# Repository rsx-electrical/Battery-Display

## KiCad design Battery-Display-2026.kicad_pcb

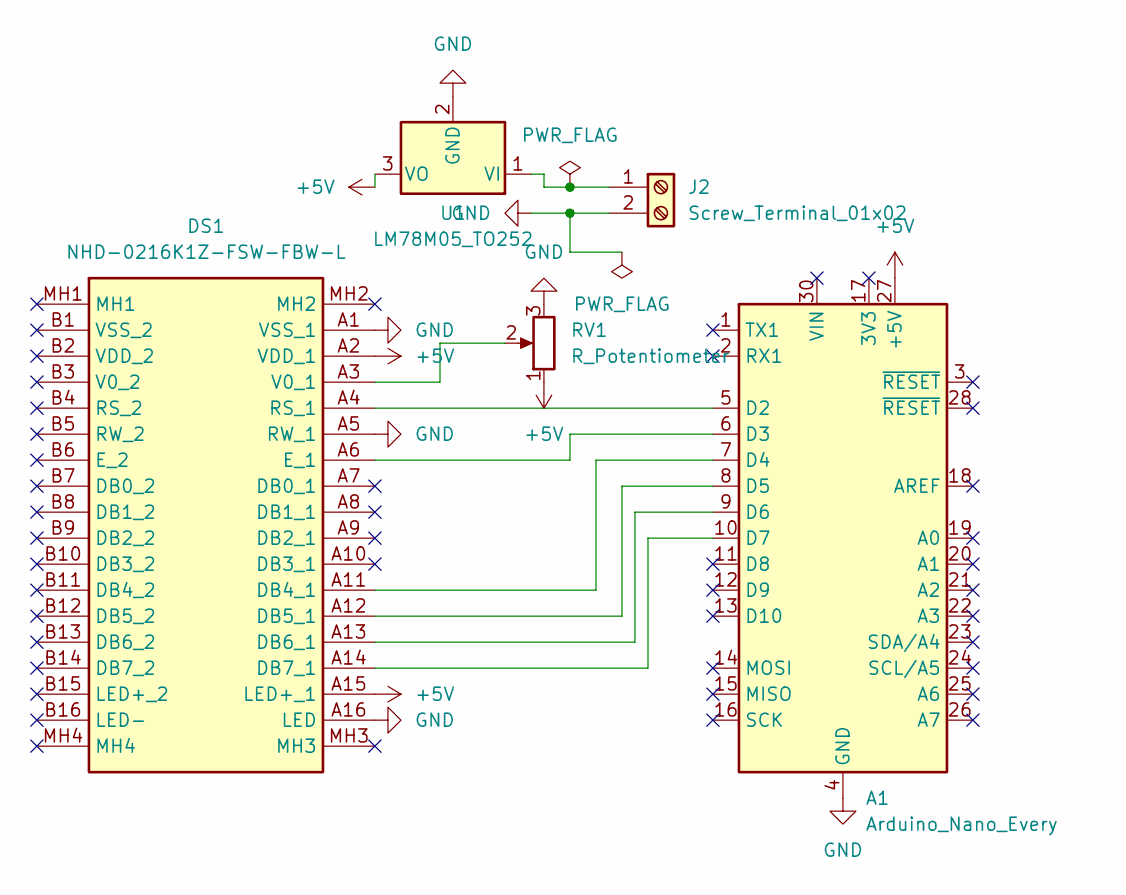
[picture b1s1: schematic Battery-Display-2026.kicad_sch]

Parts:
A1: Arduino_Nano_Every; Arduino_Nano
DS1: NHD-0216K1Z-FSW-FBW-L; NHD0216K1ZFSWFBWL; Mouser Part Number 763-0216K1Z-FSW-FBW
J2: Screw_Terminal_01x02; TerminalBlock_Phoenix_MKDS-1,5-2_1x02_P5.00mm_Horizontal
RV1: R_Potentiometer; R_Array_SIP4
U1: LM78M05_TO252; TO-252-2

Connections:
+5V: A1.27 (+5V), DS1.A2 (VDD_1), DS1.A15 (LED+_1), RV1.1, U1.3 (VO)
GND: A1.4 (GND), A1.29 (GND), DS1.A1 (VSS_1), DS1.A5 (RW_1), DS1.A16 (LED), J2.2, RV1.3, U1.2 (GND)
unnamed: A1.5 (D2), DS1.A4 (RS_1)
unnamed: A1.6 (D3), DS1.A6 (E_1)
unnamed: A1.7 (D4), DS1.A11 (DB4_1)
unnamed: A1.8 (D5), DS1.A12 (DB5_1)
unnamed: A1.9 (D6), DS1.A13 (DB6_1)
unnamed: A1.10 (D7), DS1.A14 (DB7_1)
unnamed: DS1.A3 (V0_1), RV1.2
unnamed: J2.1, U1.1 (VI)

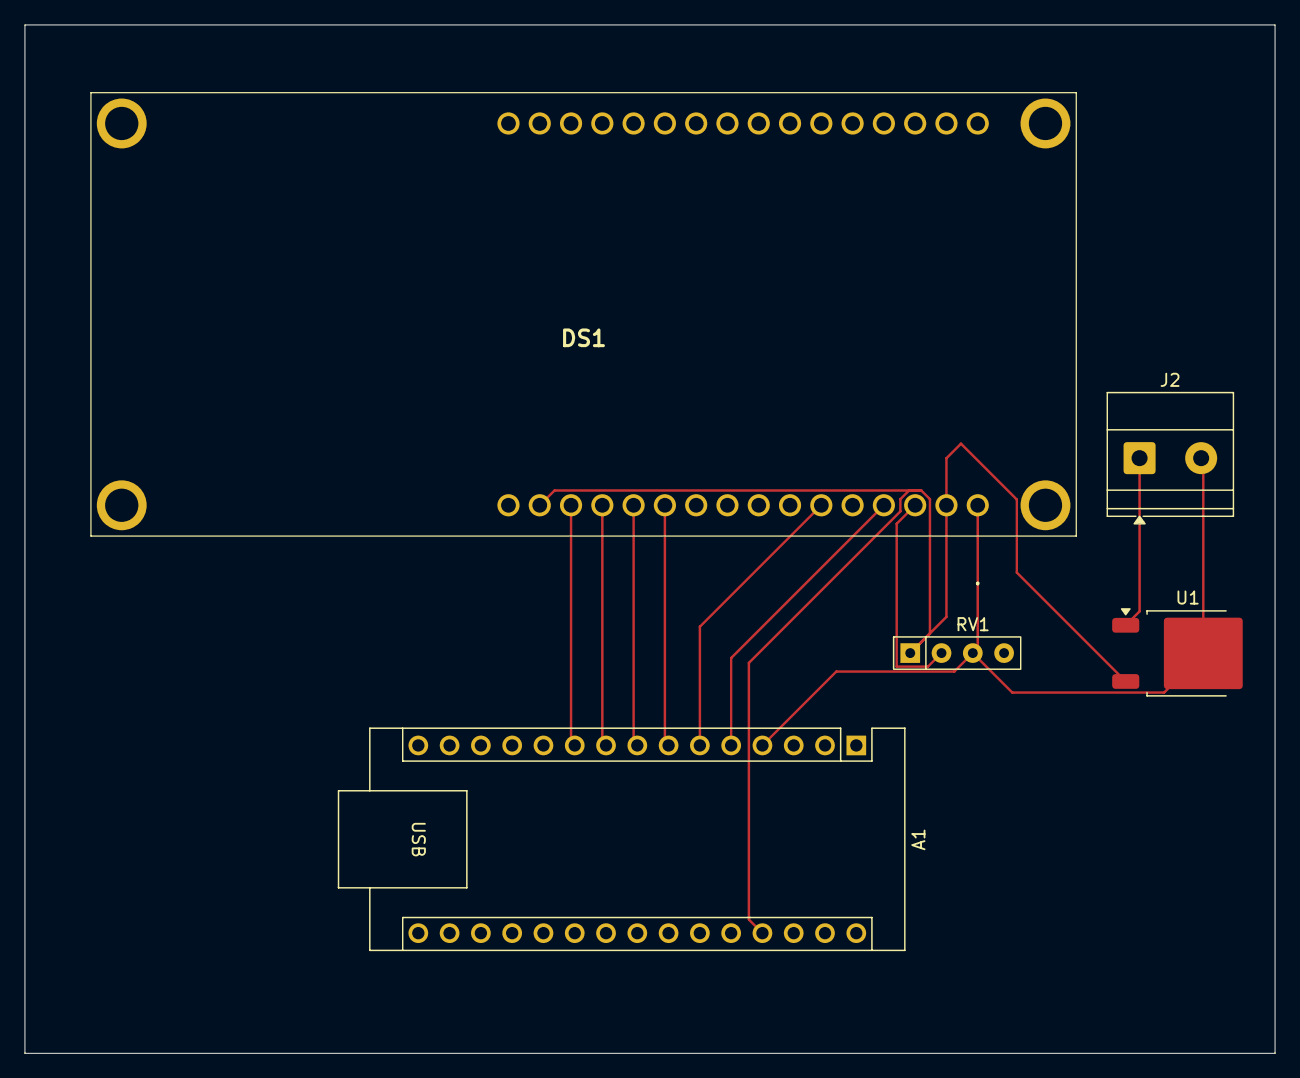
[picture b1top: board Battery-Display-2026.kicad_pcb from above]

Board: 2 copper layers, 101.5 x 83.5 mm, 5 parts (0 on the bottom side), 10 nets.

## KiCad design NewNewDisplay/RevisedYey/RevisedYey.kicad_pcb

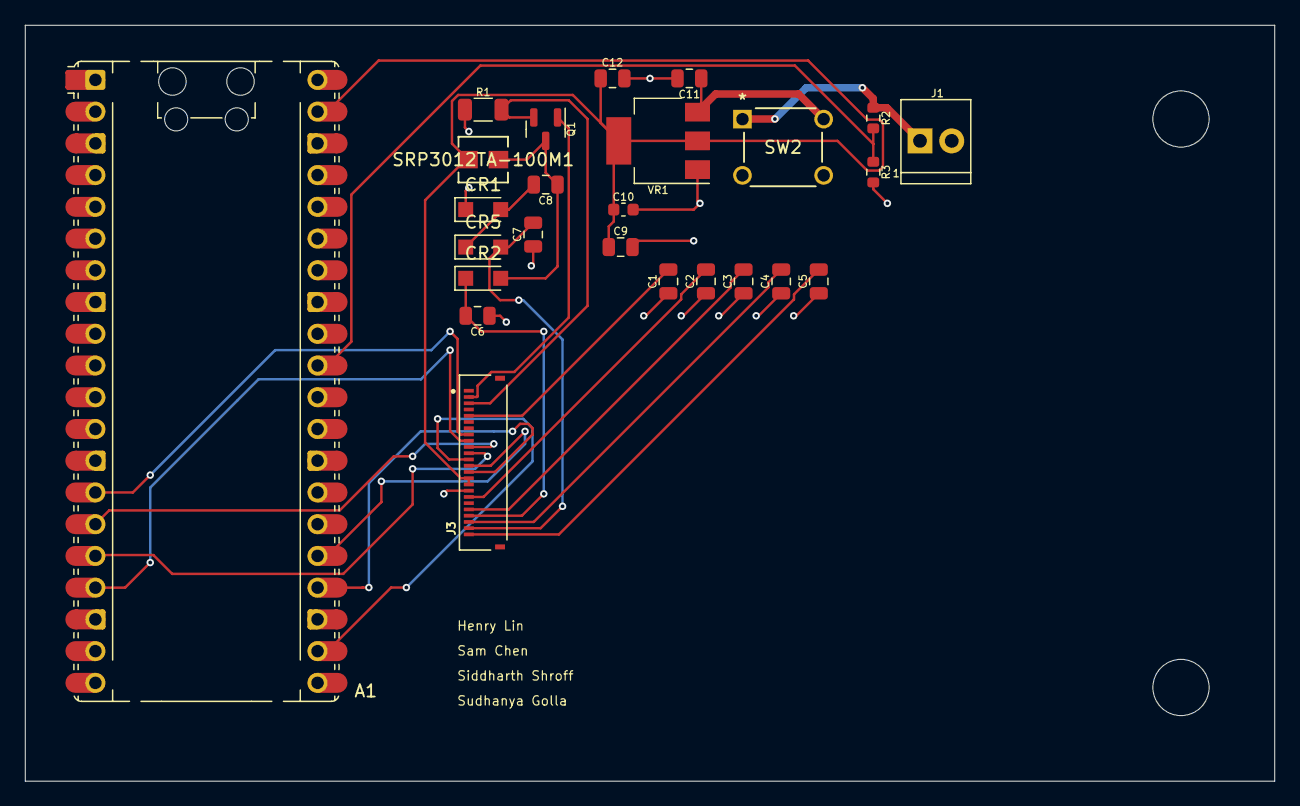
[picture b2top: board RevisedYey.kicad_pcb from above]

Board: 2 copper layers, 100.0 x 60.5 mm, 27 parts (0 on the bottom side), 23 nets.

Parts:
A1: RaspberryPi_Pico; RaspberryPi_Pico_Common_Unspecified
C1, C2, C3, C4, C5, C6, C7: 1u; C_0805_2012Metric
C8, C9: 4u7; C_0805_2012Metric
C10: 0u1; C_0603_1608Metric
C11, C12: 10u; C_0805_2012Metric
CR1, CR2, CR5: SS2040FL_R1_00001; Nexperia_CFP3_SOD-123W
H1, H2: M4 PLAIN; MountingHole_4.5mm
J1: Screw_Terminal_2x2.54; Wurth_691210910002
J3: FH34SRJ-24S-0.5SH_99_; HRS_FH34SRJ-24S-0.5SH_99_
Q1: ZXM61N03F; SOT-23
R1: 0.47R; R_1206_3216Metric
R2: 1M; R_0603_1608Metric
R3: 249K_0.1%; R_0603_1608Metric
SRP3012TA-100M1: 10uH; IND_SRP3012TA_BRN
SW2: Button-THT - 2-1825910-7; 2-1825910-7
VR1: NCP1117-3.3V; SOT-223-3_TabPin2

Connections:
+16V: J1.1, R2.1, SW2.1
GND: A1.3 (GND), A1.8 (GND), A1.13 (GND), A1.18 (GND), A1.23 (GND), A1.28 (GND), A1.38 (GND), C1.1, C2.1, C3.1, C4.1, C5.1, C6.1, C7.1, C9.2, C10.2, C11.2, C12.2, CR1.1, J1.2, J3.17, R1.1, R3.2, VR1.1 (GND)
GP10 - Pin 8 BS: A1.14 (GPIO10), J3.8
GP11 - Pin 10 RST: A1.15 (GPIO11), J3.10
GP12 - Pin 11 DC: A1.16 (GPIO12), J3.11
GP13 - Pin 9 Busy: A1.17 (GPIO13), J3.9
GP17 - Pin 12 CSB: A1.22 (GPIO17), J3.12
GP18 - Pin 14 SDA: A1.24 (GPIO18), J3.14
GP19 - Pin 13 SCL: A1.25 (GPIO19), J3.13
unnamed: C1.2, J3.5
unnamed: C2.2, J3.18
unnamed: C3.2, J3.20
unnamed: C4.2, J3.22
unnamed: C5.2, J3.24
unnamed: C6.2, CR2.1, J3.21
unnamed: C7.2, CR5.2, J3.23
unnamed: C8.2, CR1.2, CR5.1
unnamed: C8.1, CR2.2, Q1.3 (D), SRP3012TA-100M1.2
unnamed: J3.2, Q1.1 (G)
unnamed: J3.3, Q1.2 (S), R1.2
unnamed: C11.1, SW2.2, VR1.3 (VI)
PWR Board/Pico: A1.39 (VSYS), C9.1, C10.1, C12.1, J3.15, J3.16, SRP3012TA-100M1.1, VR1.2 (VO)
Vdiv pico: A1.31 (GPIO26_ADC0), R2.2, R3.1

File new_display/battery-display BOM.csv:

"Reference","Qty","Value","DNP","Exclude from BOM","Exclude from Board","Footprint","Datasheet"
"A1","1","RaspberryPi_Pico","","","","Module:RaspberryPi_Pico_Common_Unspecified","https://datasheets.raspberrypi.com/pico/pico-datasheet.pdf"
"C1,C2,C3,C4,C5,C6,C7","7","1u","","","","rsx_capacitors:C_0805_2012Metric","~"
"C8,C9","2","4u7","","","","rsx_capacitors:C_0805_2012Metric","~"
"C10","1","0u1","","","","rsx_capacitors:C_0603_1608Metric","~"
"C11,C12,C13","3","10u","","","","rsx_capacitors:C_0805_2012Metric","~"
"CR1,CR2,CR5","3","SS2040FL_R1_00001","","","","Diode_SMD:Nexperia_CFP3_SOD-123W","https://www.panjit.com.tw/upload/datasheet/SS2020FL_SERIES.pdf"
"H1,H2,H3,H4","4","M4 PLAIN","","Excluded from BOM","","rsx_misc:MountingHole_4.5mm","~"
"J1","1","Screw_Terminal_2x2.54","","","","rsx_headers_screw:Wurth_691210910002","~"
"J3","1","FH34SRJ-24S-0.5SH_99_","","","","rsx_headers_communications:HRS_FH34SRJ-24S-0.5SH_99_",""
"Q1,Q3","2","ZXM61N03F","","","","rsx_packages_TO_SOT:SOT-23","https://www.diodes.com/assets/Datasheets/ZXM61N03F.pdf"
"R1","1","0.47R","","","","rsx_resistors:R_1206_3216Metric","https://www.yageogroup.com/content/Resource%20Library/Datash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"
"R2","1","1M","","","","rsx_resistors:R_0603_1608Metric","~"
"R3","1","249K_0.1%","","","","rsx_resistors:R_0603_1608Metric","~"
"R4","1","330R","","","","rsx_resistors:R_0603_1608Metric","~"
"R5","1","100K","","","","rsx_resistors:R_0603_1608Metric","~"
"SRP3012TA-100M1","1","10uH","","","","rsx_inductors:IND_SRP3012TA_BRN","https://www.bourns.com/docs/Product-Datasheets/SRP3012TA.pdf"
"SW2","1","Button-THT - 2-1825910-7","","","","rsx_HID:2-1825910-7","https://www.te.com/usa-en/product-2-1825910-7.datasheet.pdf"
"VR1","1","NCP1117-3.3V","","","","rsx_packages_TO_SOT:SOT-223-3_TabPin2",""

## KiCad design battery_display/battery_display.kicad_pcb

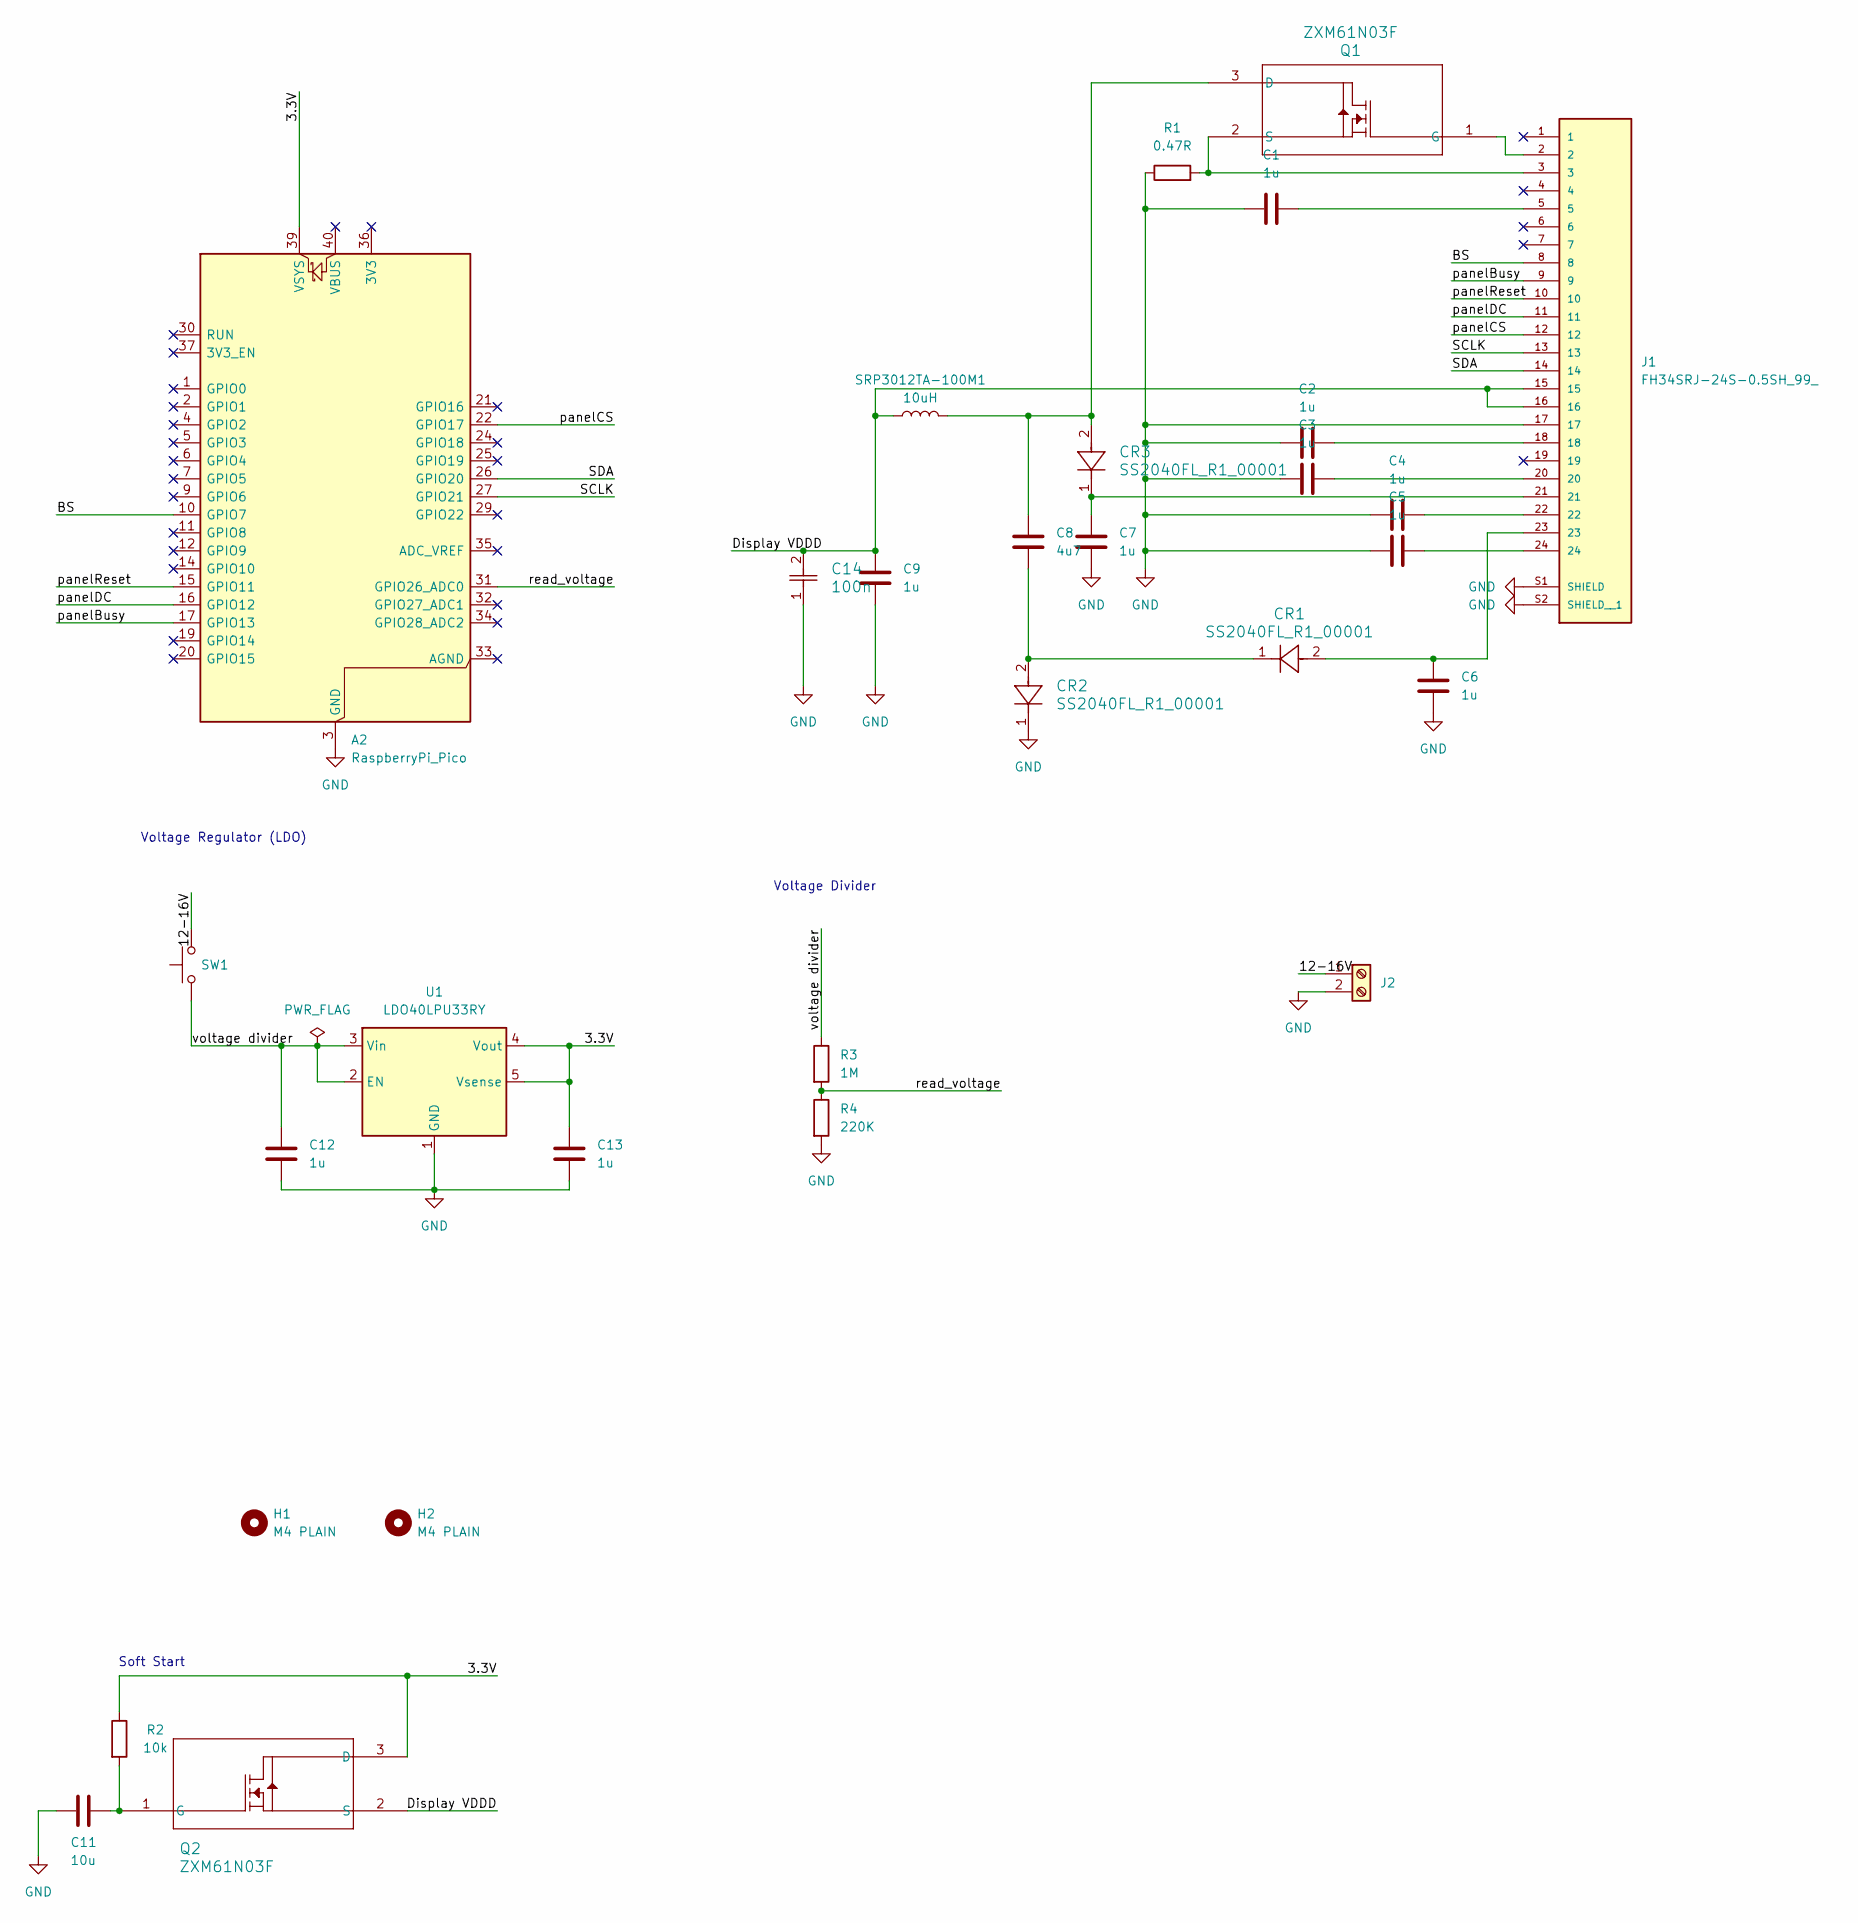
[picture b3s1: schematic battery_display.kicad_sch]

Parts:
A2: RaspberryPi_Pico; RaspberryPi_Pico_Common_Unspecified
C1, C2, C3, C4, C5, C6, C7, C9: 1u; C_0603_1608Metric; MPN CL10A105KA8NNNC
C8: 4u7; C_0805_2012Metric; MPN CL21A475KAQNNNE
C11: 10u; C_0805_2012Metric; MPN GRM21BR61H106KE43L
C12, C13: 1u; C_0805_2012Metric; MPN CL21B105KBFNNNE
C14: 100n; CAPC17595_95N_KEM; MPN C0603C104K5RACTU
CR1, CR2, CR3: SS2040FL_R1_00001; Nexperia_CFP3_SOD-123W; MPN SS2040FL_R1_00001
H1, H2: M4 PLAIN; MountingHole_4.5mm
J1: FH34SRJ-24S-0.5SH_99_; HRS_FH34SRJ-24S-0.5SH_99_; PARTREV NA
J2: Screw_Terminal_2x2.54; Wurth_691210910002; MPN 691210910002
Q1, Q2: ZXM61N03F; SOT-23; MPN ZXM61N03FTA
R1: 0.47R; R_1206_3216Metric; MPN RL1206FR-070R47L
R2: 10k; R_0603_1608Metric; MPN RMCF0603JT10K0
R3: 1M; R_0603_1608Metric; MPN ERJ-3EKF1004V
R4: 220K; R_0603_1608Metric; MPN RMCF0603FT220K
SRP3012TA-100M1: 10uH; IND_SRP3012TA_BRN; MPN SRP3012TA-100M
SW1: Button-THT - 2-1825910-7; 2-1825910-7; MPN 2-1825910-7
U1: LDO40LPU33RY; DFN-6-1EP_3x3mm_P0.95mm_EP1.7x2.6mm

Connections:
/3.3V: A2.39 (VSYS), C13.1, Q2.3 (D), R2.1, U1.4 (Vout), U1.5 (Vsense)
/12-16V: J2.1, SW1.2
/BS: A2.10 (GPIO7), J1.8
/Display VDDD: C9.1, C14.2, J1.15, J1.16, Q2.2 (S), SRP3012TA-100M1.1
/SCLK: A2.27 (GPIO21), J1.13
/SDA: A2.26 (GPIO20), J1.14
/panelBusy: A2.17 (GPIO13), J1.9
/panelCS: A2.22 (GPIO17), J1.12
/panelDC: A2.16 (GPIO12), J1.11
/panelReset: A2.15 (GPIO11), J1.10
/read_voltage: A2.31 (GPIO26_ADC0), R3.2, R4.1
/voltage divider: C12.1, R3.1, SW1.1, U1.2 (EN), U1.3 (Vin)
GND: A2.3 (GND), A2.8 (GND), A2.13 (GND), A2.18 (GND), A2.23 (GND), A2.28 (GND), A2.38 (GND), C1.1, C2.1, C3.1, C4.1, C5.1, C6.2, C7.2, C9.2, C11.2, C12.2, C13.2, C14.1, CR2.1, J1.17, J1.S1 (SHIELD), J1.S2 (SHIELD__1), J2.2, R1.1, R4.2, U1.1 (GND), U1.7 (GND)
unnamed: C1.2, J1.5
unnamed: C2.2, J1.18
unnamed: C3.2, J1.20
unnamed: C4.2, J1.22
unnamed: C5.2, J1.24
unnamed: C6.1, CR1.2, J1.23
unnamed: C7.1, CR3.1, J1.21
unnamed: C8.2, CR1.1, CR2.2
unnamed: C8.1, CR3.2, Q1.3 (D), SRP3012TA-100M1.2
unnamed: J1.2, Q1.1 (G)
unnamed: J1.3, Q1.2 (S), R1.2
unnamed: C11.1, Q2.1 (G), R2.2

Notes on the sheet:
Voltage Divider
Soft Start
Voltage Regulator (LDO)

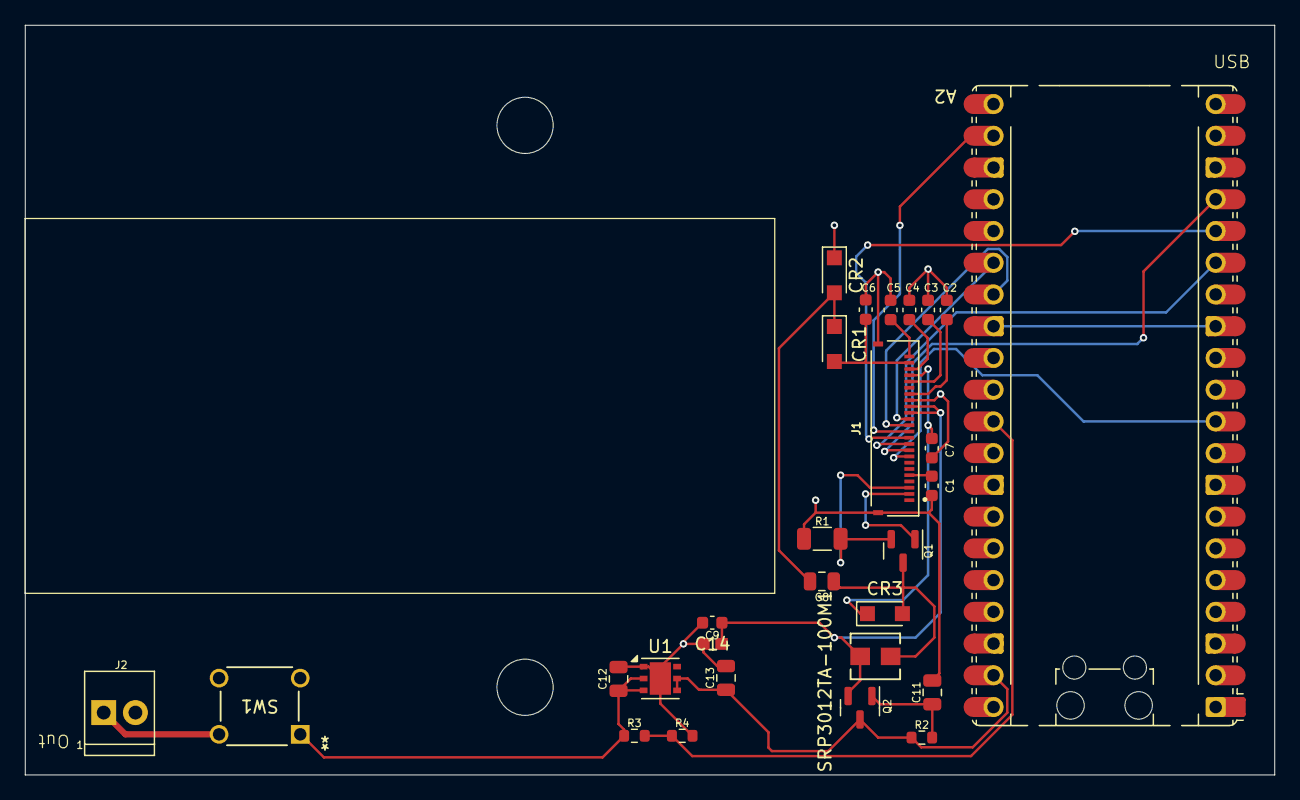
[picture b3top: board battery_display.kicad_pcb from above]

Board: 2 copper layers, 100.0 x 60.0 mm, 30 parts (0 on the bottom side), 25 nets.

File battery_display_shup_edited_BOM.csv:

"Id";"Designator";"Footprint";"Quantity";"Designation";"Supplier and ref";
1;"R1,R2";"R_1206_3216Metric";2;"0.47R";;;
2;"CR3,CR4,CR1";"Nexperia_CFP3_SOD-123W";3;"SS2040FL_R1_00001";;;
3;"Q2,Q1";"SOT-23";2;"ZXM61N03F";;;
4;"C9,C3,C6,C5,C4,C7,C1,C8,C2";"C_0805_2012Metric";9;"1u";;;
5;"VR1";"SOT-223-3_TabPin2";1;"NCP1117-3.3V";;;
6;"C10,C12";"C_0805_2012Metric";2;"10u";;;
7;"C11";"C_0603_1608Metric";1;"0u1";;;
8;"R3";"R_0603_1608Metric";1;"1M";;;
9;"SRP3012TA-100M1";"IND_SRP3012TA_BRN";1;"10uH";;;
10;"J2";"Wurth_691210910002";1;"Screw_Terminal_2x2.54";;;
11;"J1";"HRS_FH34SRJ-24S-0.5SH_99_";1;"FH34SRJ-24S-0.5SH_99_";;;
12;"R4";"R_0603_1608Metric";1;"220K";;;
13;"A1";"RaspberryPi_Pico_Common_Unspecified";1;"RaspberryPi_Pico";;;
14;"SW1";"2-1825910-7";1;"Button-THT - 2-1825910-7";;;

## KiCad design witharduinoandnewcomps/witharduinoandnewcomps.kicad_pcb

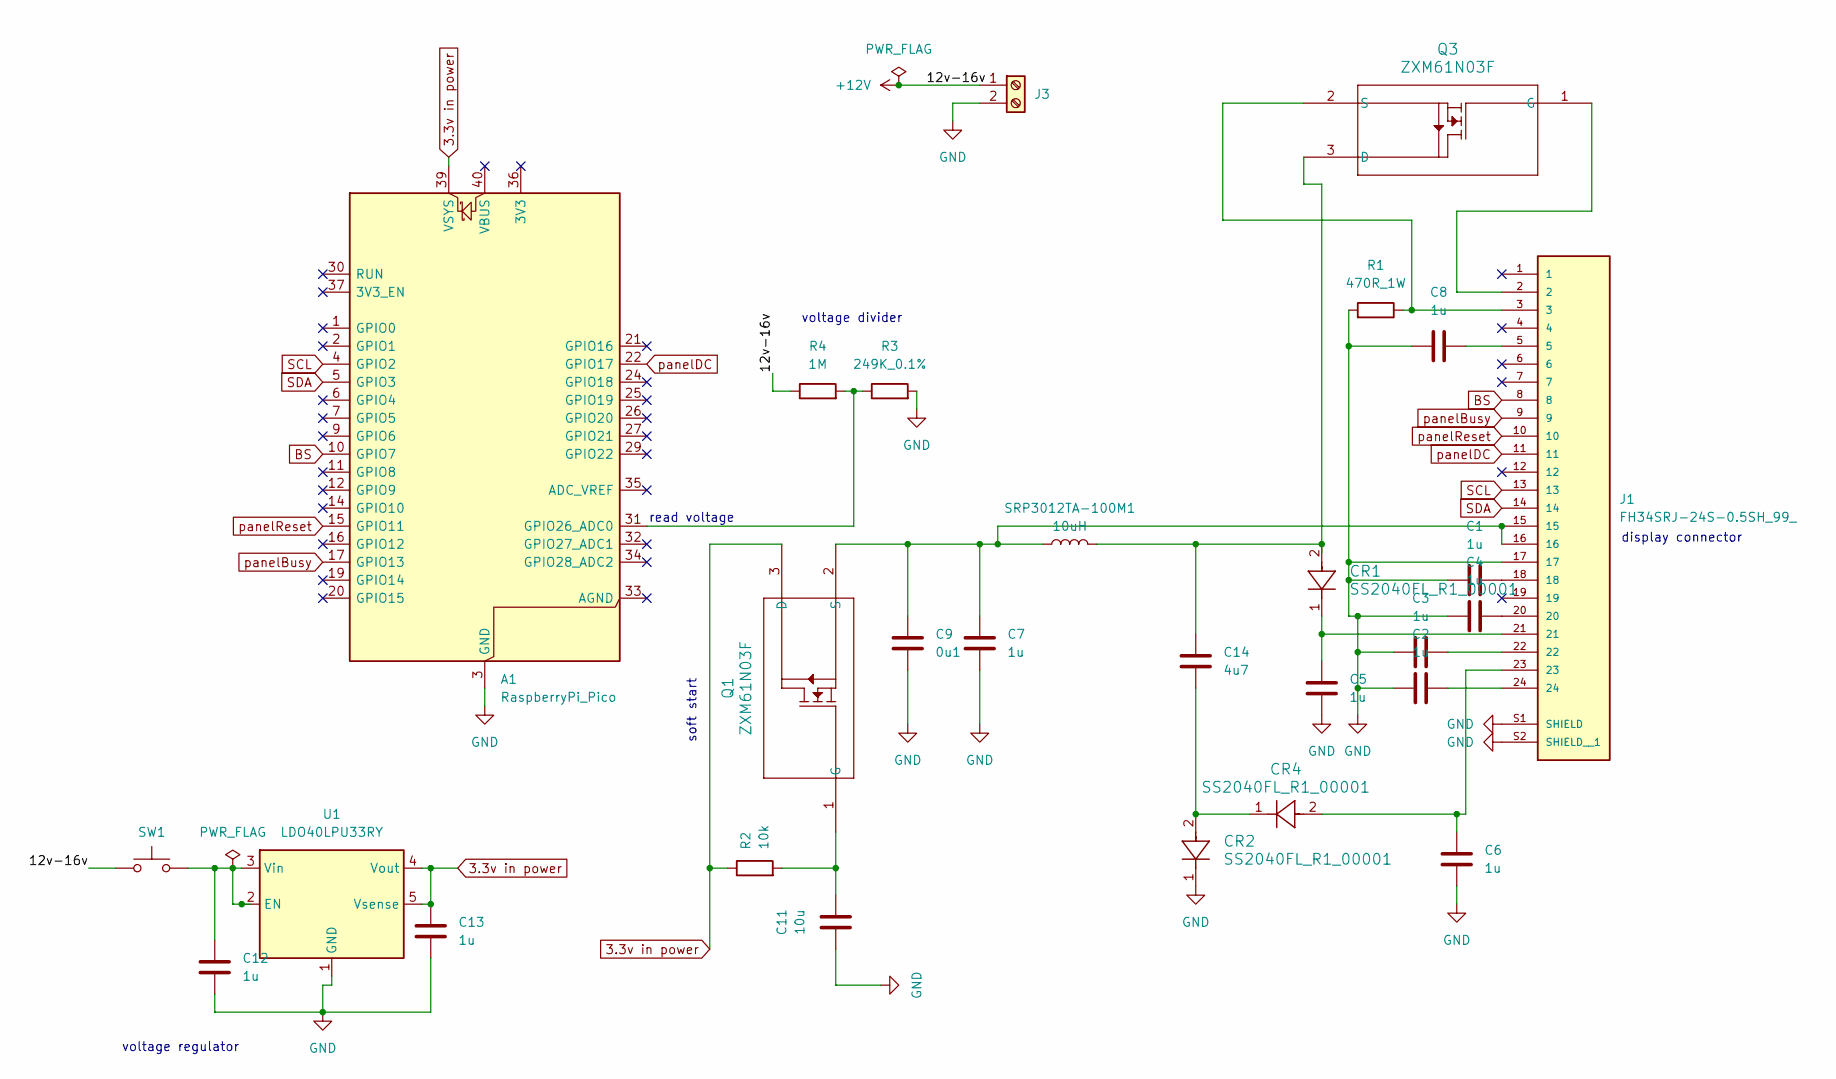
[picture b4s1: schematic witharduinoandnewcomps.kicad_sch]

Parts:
A1: RaspberryPi_Pico; RaspberryPi_Pico_Common_Unspecified
C1, C2, C3, C4, C5, C6, C7, C8, C12, C13: 1u; C_0805_2012Metric; MPN CL21B105KBFNNNE
C9: 0u1; C_0603_1608Metric; MPN C1608X7R1H104K080AA
C11: 10u; C_0805_2012Metric; MPN GRM21BR61H106KE43L
C14: 4u7; C_0805_2012Metric; MPN CL21A475KAQNNNE
CR1, CR2, CR4: SS2040FL_R1_00001; Nexperia_CFP3_SOD-123W; MPN SS2040FL_R1_00001
J1: FH34SRJ-24S-0.5SH_99_; HRS_FH34SRJ-24S-0.5SH_99_; PARTREV NA
J3: Screw_Terminal_2x2.54; Wurth_691210910002; MPN 691210910002
Q1, Q3: ZXM61N03F; SOT-23; MPN ZXM61N03FTA
R1: 470R_1W; R_2512_6332Metric; MPN RC2512FK-07470RL
R2: 10k; R_0603_1608Metric; MPN RMCF0603JT10K0
R3: 249K_0.1%; R_0603_1608Metric; MPN RC0603FR-07249KL
R4: 1M; R_0603_1608Metric; MPN ERJ-3EKF1004V
SRP3012TA-100M1: 10uH; IND_SRP3012TA_BRN; MPN SRP3012TA-100M
SW1: Button-THT - 2-1825910-7; 2-1825910-7; MPN 2-1825910-7
U1: LDO40LPU33RY; DFN-6-1EP_3x3mm_P0.95mm_EP1.7x2.6mm

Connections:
3.3v in power: A1.39 (VSYS), C13.1, Q1.3 (D), R2.1, U1.4 (Vout), U1.5 (Vsense)
+12V: J3.1, R4.1, SW1.1
BS: A1.10 (GPIO7), J1.8
GND: A1.3 (GND), A1.8 (GND), A1.13 (GND), A1.18 (GND), A1.23 (GND), A1.28 (GND), A1.38 (GND), C1.1, C2.1, C3.1, C4.1, C5.1, C6.1, C7.1, C8.1, C9.2, C11.1, C12.2, C13.2, CR2.1, J1.17, J1.S1 (SHIELD), J1.S2 (SHIELD__1), J3.2, R1.1, R3.2, U1.1 (GND), U1.7 (GND)
unnamed: A1.31 (GPIO26_ADC0), R3.1, R4.2
unnamed: C1.2, J1.18
unnamed: C2.2, J1.24
unnamed: C3.2, J1.22
unnamed: C4.2, J1.20
unnamed: C5.2, CR1.1, J1.21
unnamed: C6.2, CR4.2, J1.23
unnamed: C8.2, J1.5
unnamed: C14.2, CR2.2, CR4.1
unnamed: C11.2, Q1.1 (G), R2.2
unnamed: C7.2, C9.1, J1.15, J1.16, Q1.2 (S), SRP3012TA-100M1.1
unnamed: C14.1, CR1.2, Q3.3 (D), SRP3012TA-100M1.2
unnamed: J1.2, Q3.1 (G)
unnamed: J1.3, Q3.2 (S), R1.2
unnamed: C12.1, SW1.2, U1.2 (EN), U1.3 (Vin)
SCL: A1.4 (GPIO2), J1.13
SDA: A1.5 (GPIO3), J1.14
panelBusy: A1.17 (GPIO13), J1.9
panelDC: A1.22 (GPIO17), J1.11
panelReset: A1.15 (GPIO11), J1.10

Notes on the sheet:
soft start
voltage divider
display connector
read voltage
voltage regulator

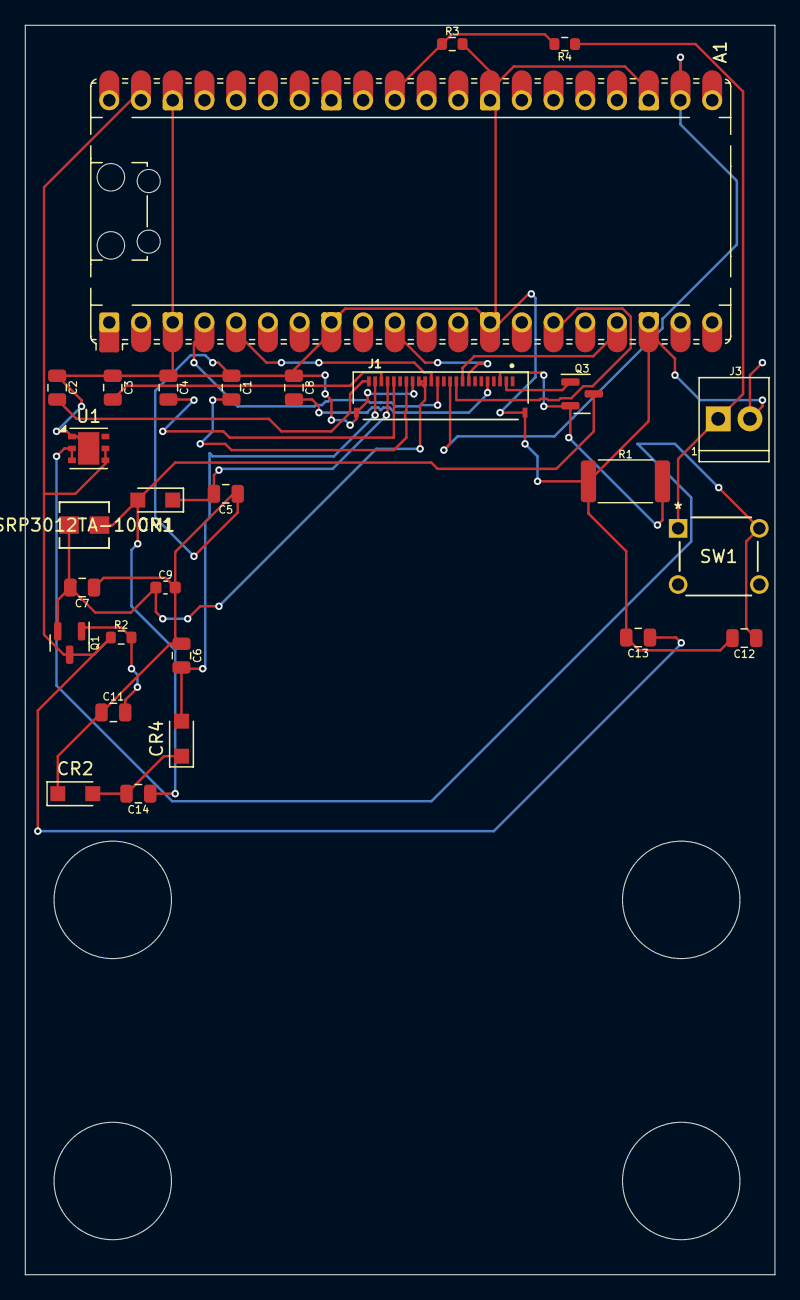
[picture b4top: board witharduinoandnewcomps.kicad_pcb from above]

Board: 2 copper layers, 60.0 x 100.0 mm, 28 parts (0 on the bottom side), 24 nets.

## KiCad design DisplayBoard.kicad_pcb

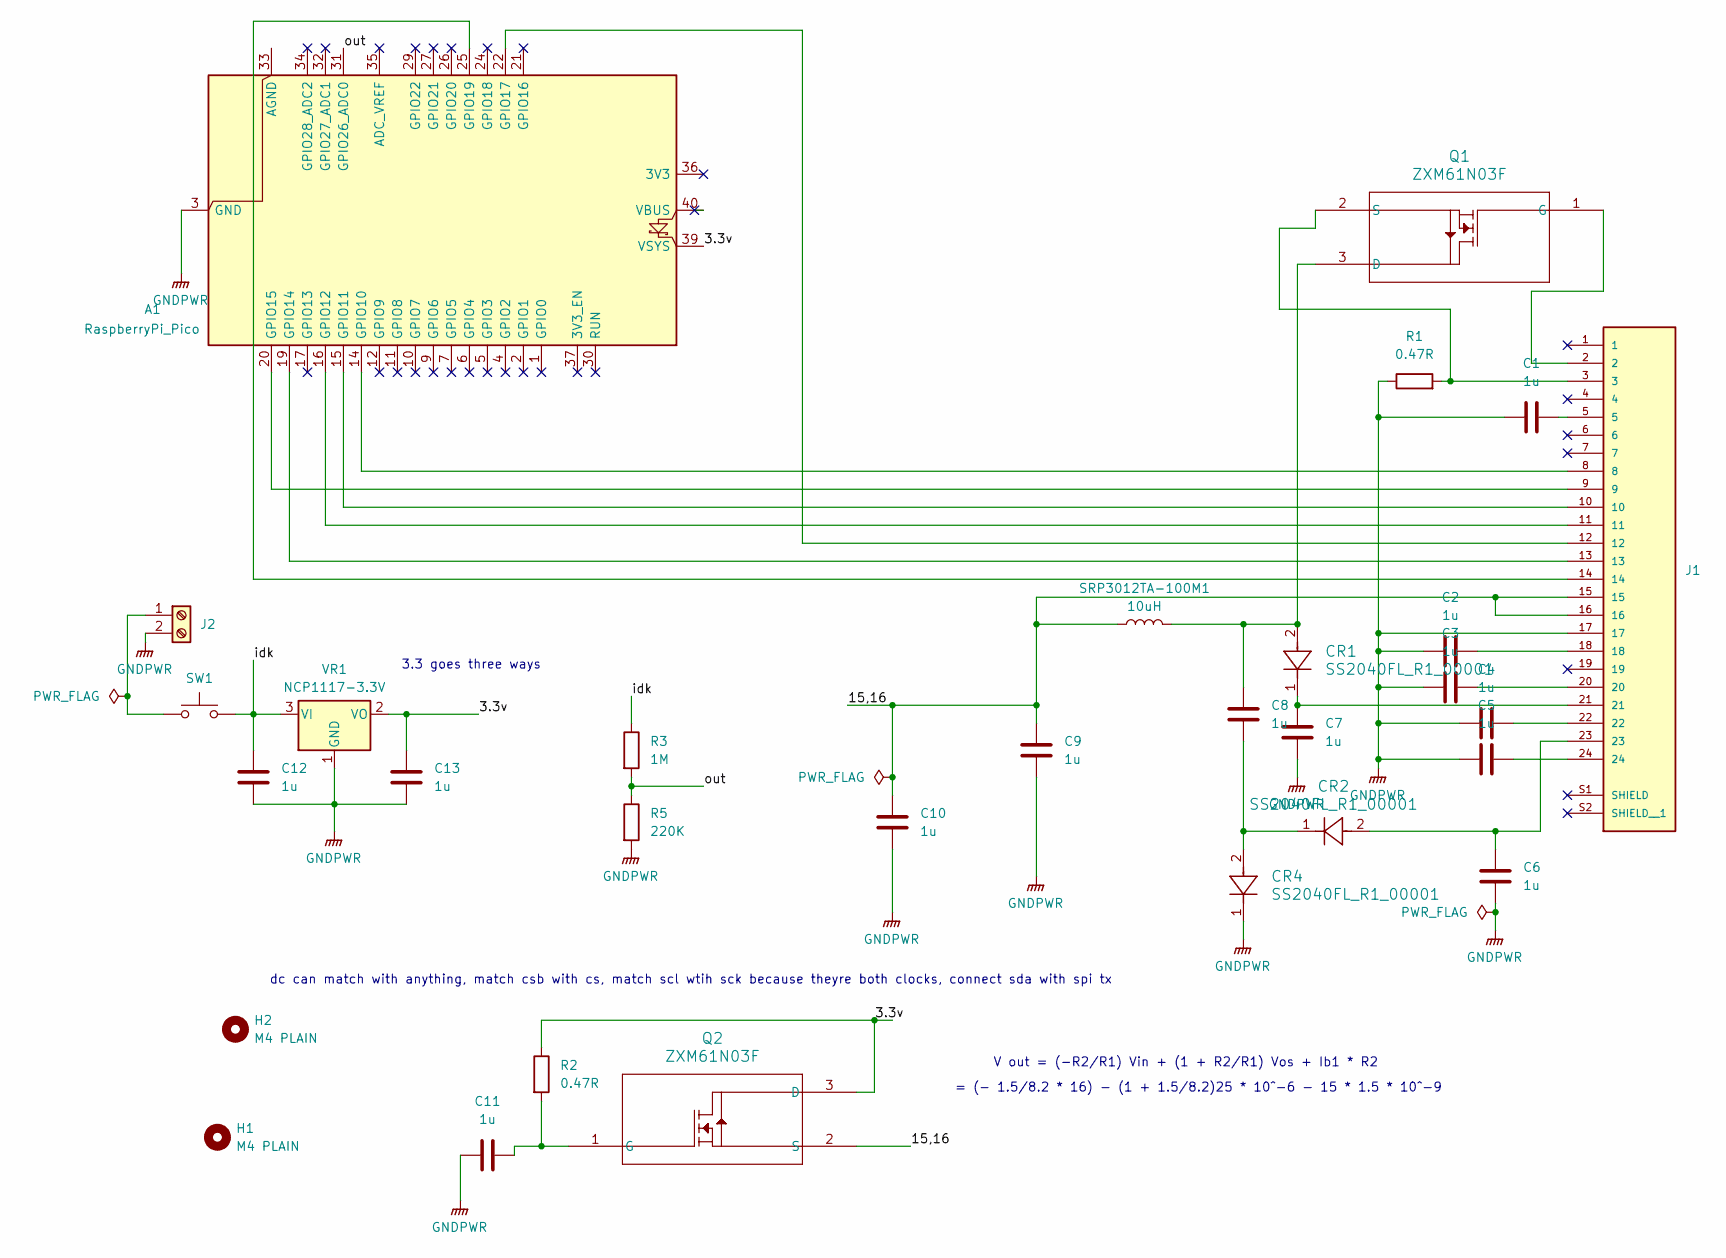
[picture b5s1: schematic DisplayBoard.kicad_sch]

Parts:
A1: RaspberryPi_Pico; RaspberryPi_Pico_Common_Unspecified
C1, C2, C3, C4, C5, C6, C7, C8, C9, C10, C11, C12, C13: 1u; C_0805_2012Metric; MPN CL21B105KBFNNNE
CR1, CR2, CR4: SS2040FL_R1_00001; Nexperia_CFP3_SOD-123W; MPN SS2040FL_R1_00001
H1, H2: M4 PLAIN; MountingHole_4.5mm
J1: FH34SRJ-24S-0.5SH_99_; HRS_FH34SRJ-24S-0.5SH_99_; PARTREV NA
J2: Screw_Terminal_2x5.08; Molex_0398800302; MPN 398800302
Q1, Q2: ZXM61N03F; SOT-23; MPN ZXM61N03FTA
R1, R2: 0.47R; R_1206_3216Metric; MPN RL1206FR-070R47L
R3: 1M; R_0603_1608Metric; MPN ERJ-3EKF1004V
R5: 220K; R_0603_1608Metric; MPN RMCF0603FT220K
SRP3012TA-100M1: 10uH; IND_SRP3012TA_BRN; MPN SRP3012TA-100M
SW1: Button; FSMSMTR; MPN FSMSMTR
VR1: NCP1117-3.3V; SOT-223-3_TabPin2; MPN NCP1117IST33T3G

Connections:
/3.3v: A1.39 (VSYS), C13.2, Q2.3 (D), R2.1, VR1.2 (VO)
/15,16: C9.1, C10.1, J1.15, J1.16, Q2.2 (S), SRP3012TA-100M1.1
/idk: C12.2, R3.1, SW1.2, VR1.3 (VI)
/out: A1.31 (GPIO26_ADC0), R3.2, R5.1
GNDPWR: A1.3 (GND), A1.8 (GND), A1.13 (GND), A1.18 (GND), A1.23 (GND), A1.28 (GND), A1.38 (GND), C1.2, C2.1, C3.1, C4.1, C5.1, C6.2, C7.2, C9.2, C10.2, C11.2, C12.1, C13.1, CR4.1, J1.17, J2.2, R1.1, R5.2, VR1.1 (GND)
unnamed: A1.14 (GPIO10), J1.8
unnamed: A1.15 (GPIO11), J1.10
unnamed: A1.16 (GPIO12), J1.11
unnamed: A1.19 (GPIO14), J1.13
unnamed: A1.20 (GPIO15), J1.9
unnamed: A1.22 (GPIO17), J1.12
unnamed: A1.25 (GPIO19), J1.14
unnamed: C1.1, J1.5
unnamed: C2.2, J1.18
unnamed: C3.2, J1.20
unnamed: C4.2, J1.22
unnamed: C5.2, J1.24
unnamed: C6.1, CR2.2, J1.23
unnamed: C7.1, CR1.1, J1.21
unnamed: C8.2, CR2.1, CR4.2
unnamed: J2.1, SW1.1
unnamed: C8.1, CR1.2, Q1.3 (D), SRP3012TA-100M1.2
unnamed: J1.2, Q1.1 (G)
unnamed: J1.3, Q1.2 (S), R1.2
unnamed: C11.1, Q2.1 (G), R2.2

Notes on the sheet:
3.3 goes three ways
V out = (-R2/R1) Vin + (1 + R2/R1) Vos + Ib1 * R2
= (- 1.5/8.2 * 16) - (1 + 1.5/8.2)25 * 10^-6 - 15 * 1.5 * 10^-9
dc can match with anything, match csb with cs, match scl wtih sck because theyre both clocks, connect sda with spi tx

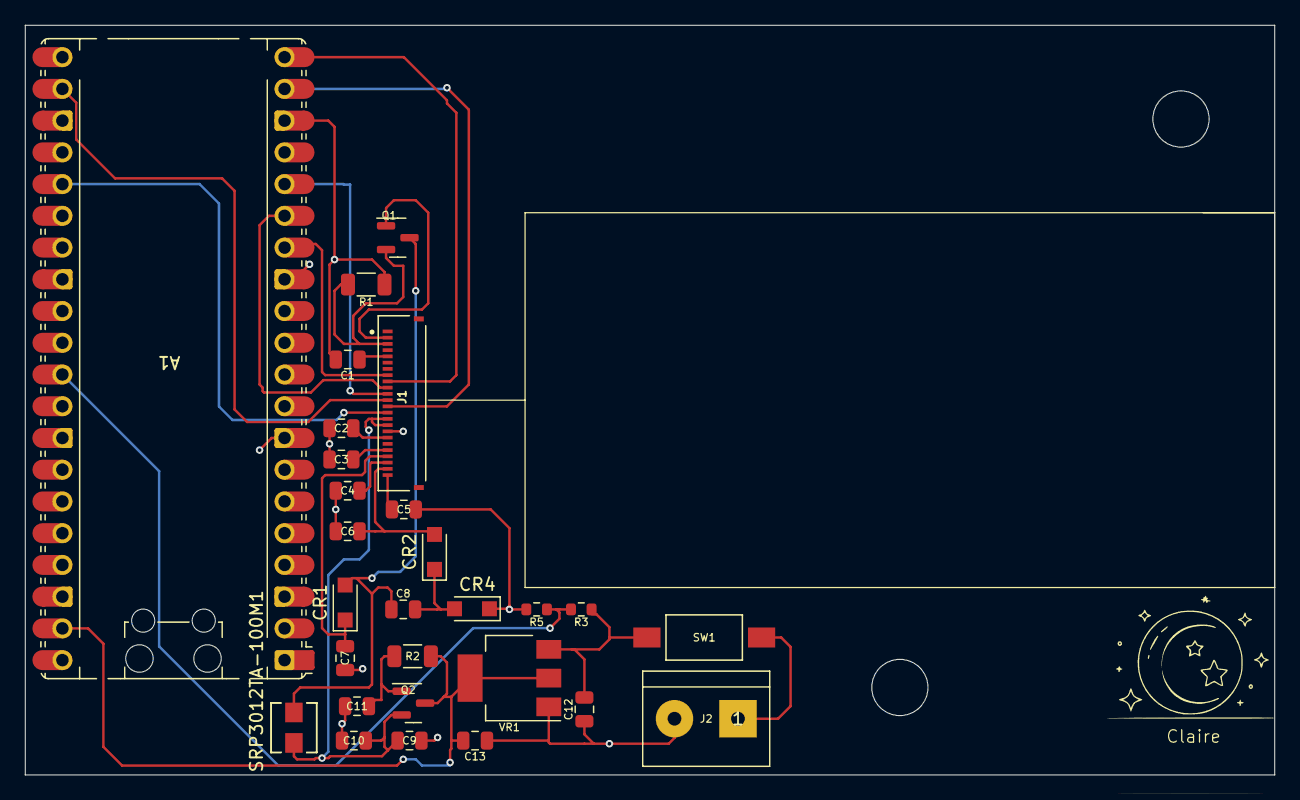
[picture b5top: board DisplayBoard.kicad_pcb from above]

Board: 2 copper layers, 100.0 x 60.0 mm, 30 parts (0 on the bottom side), 25 nets.
